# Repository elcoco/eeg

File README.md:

EEG
===

This project is about creating an EEG device based  
on the ADS1299 chip and a raspberrypi 2.  
In this repository you'll find cad files for making  
the PCB and also the software.  
It is a work in progress and is nowhere near finished.

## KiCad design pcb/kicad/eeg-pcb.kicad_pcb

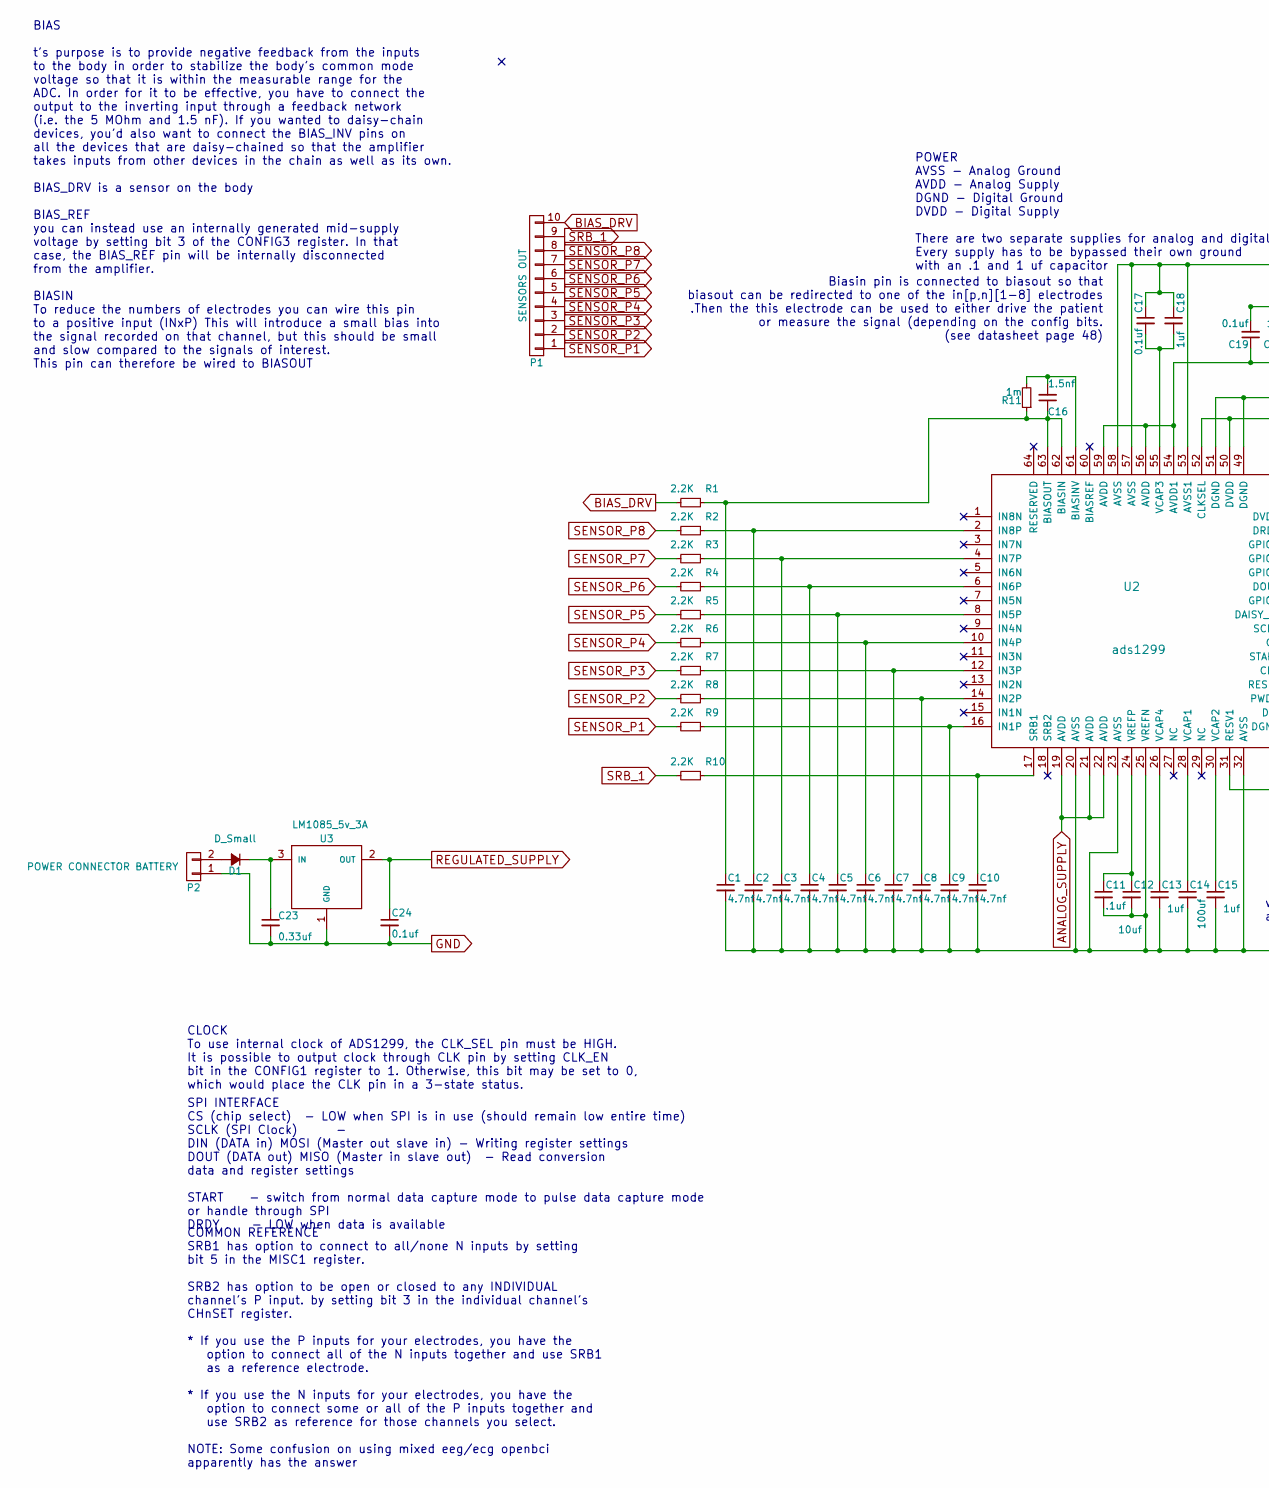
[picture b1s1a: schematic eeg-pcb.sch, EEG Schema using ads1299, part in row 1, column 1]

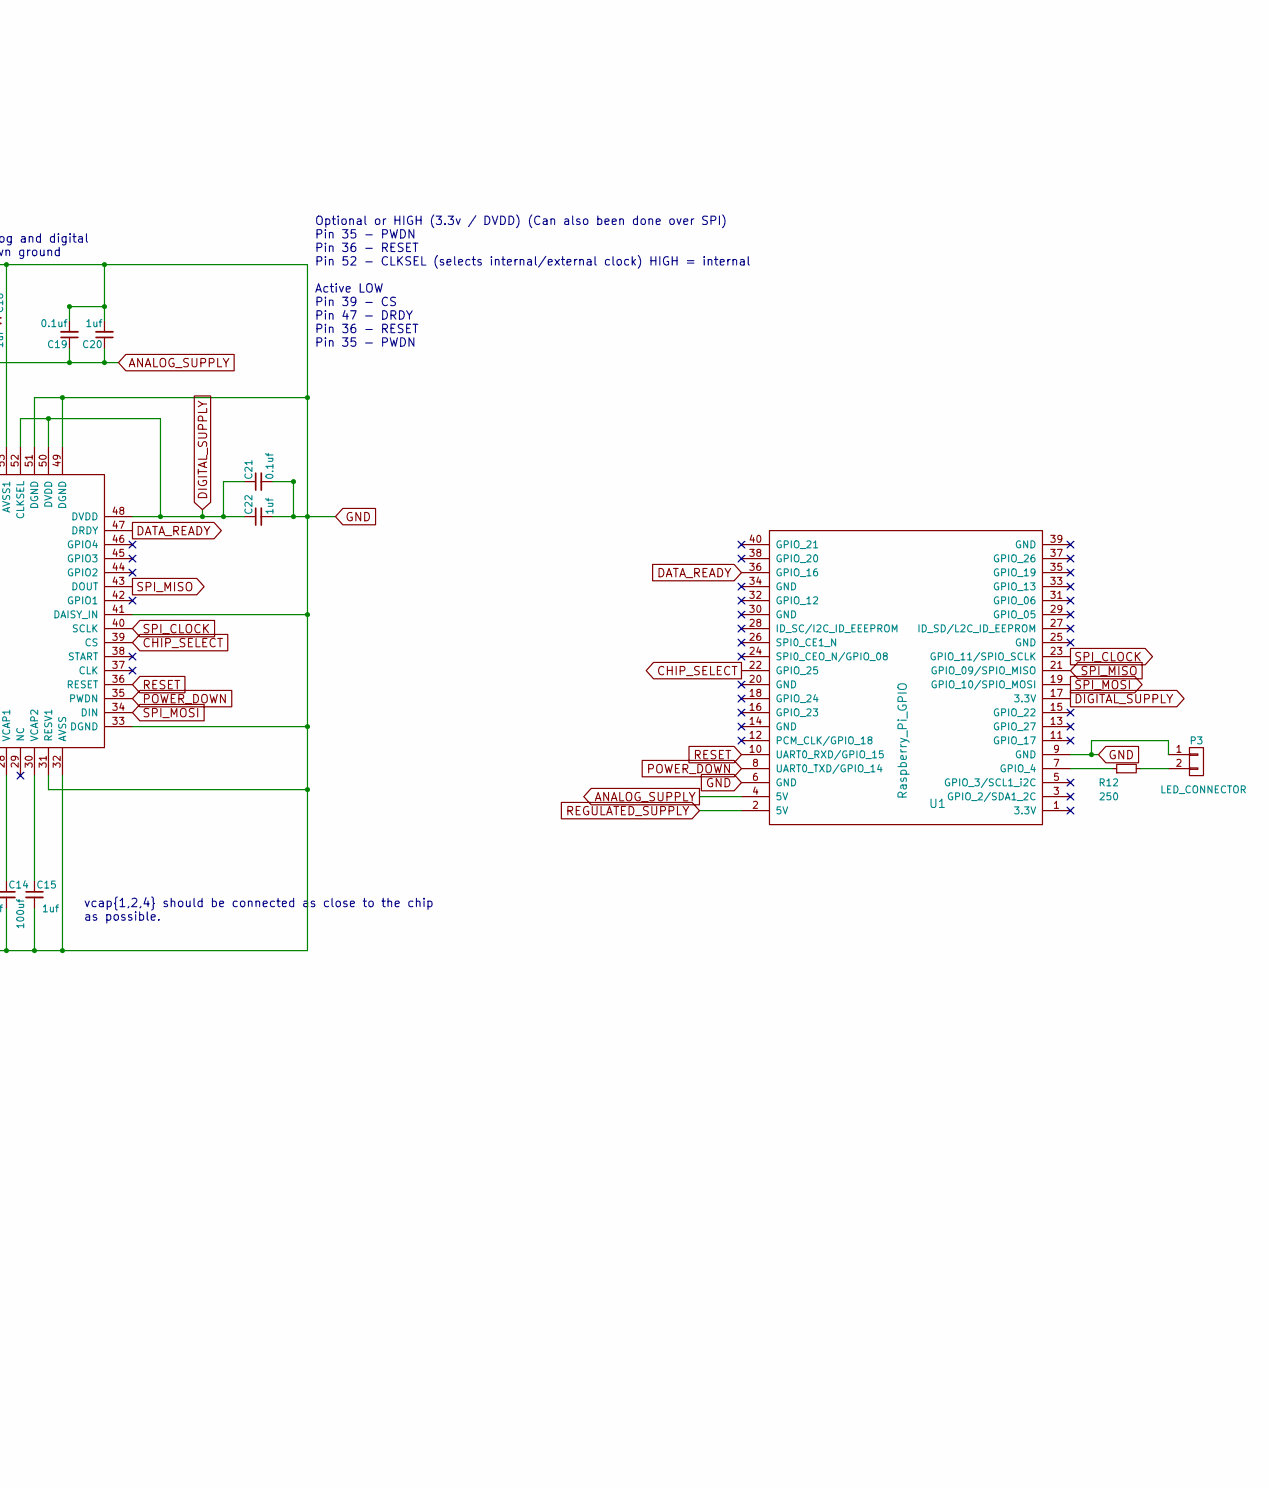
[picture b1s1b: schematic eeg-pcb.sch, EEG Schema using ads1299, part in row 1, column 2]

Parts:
C1, C2, C3, C4, C5, C6, C7, C8, C9, C10: 4.7nf; C_0603_HandSoldering
C11: .1uf; C_0603_HandSoldering
C12: 10uf; C_0603_HandSoldering
C13, C15, C18, C20, C22: 1uf; C_0603_HandSoldering
C14: 100uf; C_0603_HandSoldering
C16: 1.5nf; C_0603_HandSoldering
C17, C19, C21, C24: 0.1uf; C_0603_HandSoldering
C23: 0.33uf; C_0603_HandSoldering
D1: D_Small; 1n1008
P1: SENSORS OUT; Pin_Header_Straight_1x10
P2: POWER CONNECTOR BATTERY; Pin_Header_Straight_1x02
P3: LED_CONNECTOR; Pin_Header_Straight_1x02
R1, R2, R3, R4, R5, R6, R7, R8, R9, R10: 2.2K; R_0603_HandSoldering
R11: 1m; R_0603_HandSoldering
R12: 250; R_0603_HandSoldering
U1: Raspberry_Pi_GPIO; Pin_Header_Straight_2x20
U2: ads1299
U3: LM1085_5v_3A; LM1085

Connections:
ANALOG_SUPPLY: C19.1, C20.1, U1.4 (5V), U2.19 (AVDD), U2.21 (AVDD), U2.22 (AVDD), U2.54 (AVDD1), U2.56 (AVDD), U2.59 (AVDD)
BIAS_DRV: P1.10, R1.2
CHIP_SELECT: U1.22 (GPIO_25), U2.39 (CS)
DATA_READY: U1.36 (GPIO_16), U2.47 (DRDY)
DIGITAL_SUPPLY: C21.1, C22.1, U1.17 (3.3V), U2.48 (DVDD), U2.50 (DVDD), U2.52 (CLKSEL)
GND: C1.2, C2.2, C3.2, C4.2, C5.2, C6.2, C7.2, C8.2, C9.2, C10.2, C11.2, C12.2, C13.2, C14.2, C15.2, C17.1, C18.1, C19.2, C20.2, C21.2, C22.2, C23.2, C24.2, P2.1, P3.1, U1.6 (GND), U1.9 (GND), U2.20 (AVSS), U2.23 (AVSS), U2.25 (VREFN), U2.31 (RESV1), U2.32 (AVSS), U2.33 (DGND), U2.41 (DAISY_IN), U2.49 (DGND), U2.51 (DGND), U2.53 (AVSS1), U2.57 (AVSS), U2.58 (AVSS), U3.1 (GND)
unnamed: C1.1, C16.1, R1.1, R11.1, U2.62 (BIASIN), U2.63 (BIASOUT)
unnamed: C2.1, R2.1, U2.2 (IN8P)
unnamed: C3.1, R3.1, U2.4 (IN7P)
unnamed: C4.1, R4.1, U2.6 (IN6P)
unnamed: C5.1, R5.1, U2.8 (IN5P)
unnamed: C6.1, R6.1, U2.10 (IN4P)
unnamed: C7.1, R7.1, U2.12 (IN3P)
unnamed: C8.1, R8.1, U2.14 (IN2P)
unnamed: C9.1, R9.1, U2.16 (IN1P)
unnamed: C10.1, R10.1, U2.17 (SRB1)
unnamed: C11.1, C12.1, U2.24 (VREFP)
unnamed: C13.1, U2.26 (VCAP4)
unnamed: C14.1, U2.28 (VCAP1)
unnamed: C15.1, U2.30 (VCAP2)
unnamed: C16.2, R11.2, U2.61 (BIASINV)
unnamed: C17.2, C18.2, U2.55 (VCAP3)
unnamed: C23.1, D1.1 (K), U3.3 (IN)
unnamed: D1.2 (A), P2.2
unnamed: P3.2, R12.2
unnamed: R12.1, U1.7 (GPIO_4)
POWER_DOWN: U1.8 (UART0_TXD/GPIO_14), U2.35 (PWDN)
REGULATED_SUPPLY: C24.1, U1.2 (5V), U3.2 (OUT)
RESET: U1.10 (UART0_RXD/GPIO_15), U2.36 (RESET)
SENSOR_P1: P1.1, R9.2
SENSOR_P2: P1.2, R8.2
SENSOR_P3: P1.3, R7.2
SENSOR_P4: P1.4, R6.2
SENSOR_P5: P1.5, R5.2
SENSOR_P6: P1.6, R4.2
SENSOR_P7: P1.7, R3.2
SENSOR_P8: P1.8, R2.2
SPI_CLOCK: U1.23 (GPIO_11/SPIO_SCLK), U2.40 (SCLK)
SPI_MISO: U1.21 (GPIO_09/SPIO_MISO), U2.43 (DOUT)
SPI_MOSI: U1.19 (GPIO_10/SPIO_MOSI), U2.34 (DIN)
SRB_1: P1.9, R10.2

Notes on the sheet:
Optional or HIGH (3.3v / DVDD) (Can also been done over SPI) Pin 35 - PWDN Pin 36 - RESET Pin 52 - CLKSEL (selects internal/external clock) HIGH = internal Active LOW Pin 39 - CS Pin 47 - DRDY Pin 36 - RESET Pin 35 - PWDN
BIAS t's purpose is to provide negative feedback from the inputs to the body in order to stabilize the body's common mode voltage so that it is within the measurable range for the ADC. In order for it to be effective, you have to connect the output to the inverting input through a feedback network 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
COMMON REFERENCE SRB1 has option to connect to all/none N inputs by setting bit 5 in the MISC1 register. SRB2 has option to be open or closed to any INDIVIDUAL channel's P input. by setting bit 3 in the individual channel's CHnSET register. * If you use the P inputs for your electrodes, you have th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
SPI INTERFACE CS (chip select) - LOW when SPI is in use (should remain low entire time) SCLK (SPI Clock) - DIN (DATA in) MOSI (Master out slave in) - Writing register settings DOUT (DATA out) MISO (Master in slave out) - Read conversion data and register settings START - switch from normal data cap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
POWER AVSS - Analog Ground AVDD - Analog Supply DGND - Digital Ground DVDD - Digital Supply There are two separate supplies for analog and digital Every supply has to be bypassed their own ground with an .1 and 1 uf capacitor
CLOCK To use internal clock of ADS1299, the CLK_SEL pin must be HIGH. It is possible to output clock through CLK pin by setting CLK_EN bit in the CONFIG1 register to 1. Otherwise, this bit may be set to 0, which would place the CLK pin in a 3-state status.
vcap{1,2,4} should be connected as close to the chip as possible.
Biasin pin is connected to biasout so that biasout can be redirected to one of the in[p,n][1-8] electrodes .Then the this electrode can be used to either drive the patient or measure the signal (depending on the config bits. (see datasheet page 48)

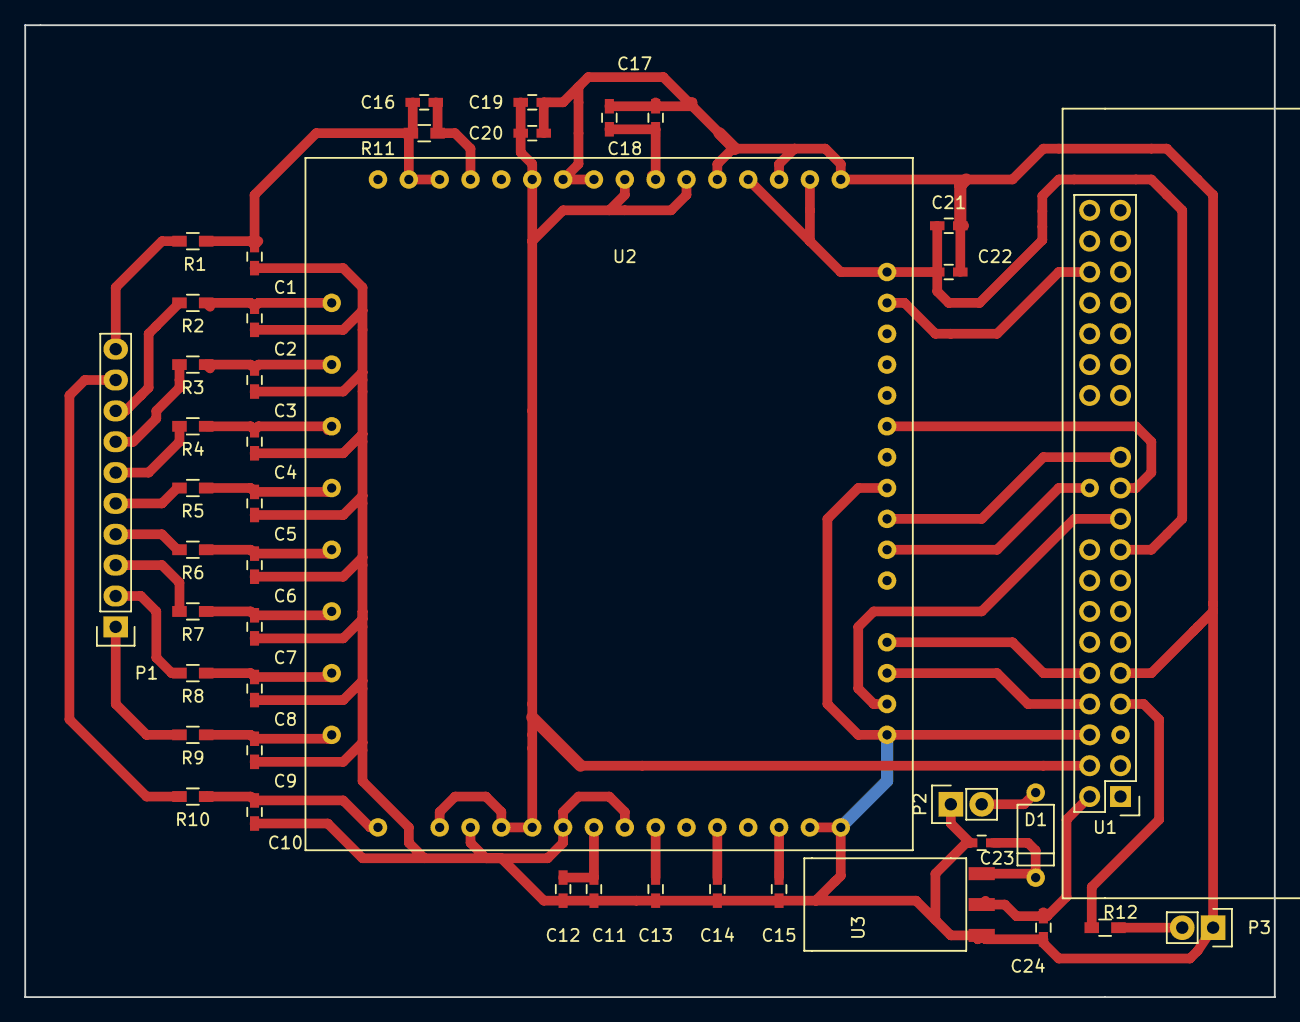
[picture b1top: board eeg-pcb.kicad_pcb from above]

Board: 2 copper layers, 102.9 x 80.0 mm, 43 parts (0 on the bottom side), 41 nets.

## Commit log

2016-02-10 first
2016-02-10 "update"
